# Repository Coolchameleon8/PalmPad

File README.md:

PalmPad
A single handed keyboard based on the hackclub hackpad. Uses a resistor ladder and custom qmk firmware to allow for more inputs than the seeduino xiao has room for.
This is still a work in progress and the case is just temporary. The final version will look similar to a joystick. It is however difficult to design the joystick without the pcb as it has to be broken into parts. This document will be updated later on.

Prototype of the palmpad, just used to test electronics and clearances.
Onshape Link:
https://cad.onshape.com/documents/9e26ee7e9571adbf7a7901c8/w/e33cc611a5f829e6b25b9a69/e/7c23ee493dd5f25881813654?renderMode=0&uiState=69e04b46a869df219ed1fa1f

Wiring schematic for the palmpad

The PCB design

How the case fits together

BOM:
*Seeeduino xiao rp2040
*16x SK6812 MINI-E LEDs
*2x EC11 Rotary encoders
*14x MX-Style switches
*10x through-hole 1N4148 Diodes
*1x 0.91 inch OLED display
*14x white blank DSA keycaps
*4x M3x16mm screws

NOT in hackpad kit
*Assorted wire
*6 10nF smd 1206 capacitors
*6 1k Ohm smd 1206 capacitors
*7 200k Ohm smd 1206 capacitors
*5 100k Ohm smd 1206 capacitors

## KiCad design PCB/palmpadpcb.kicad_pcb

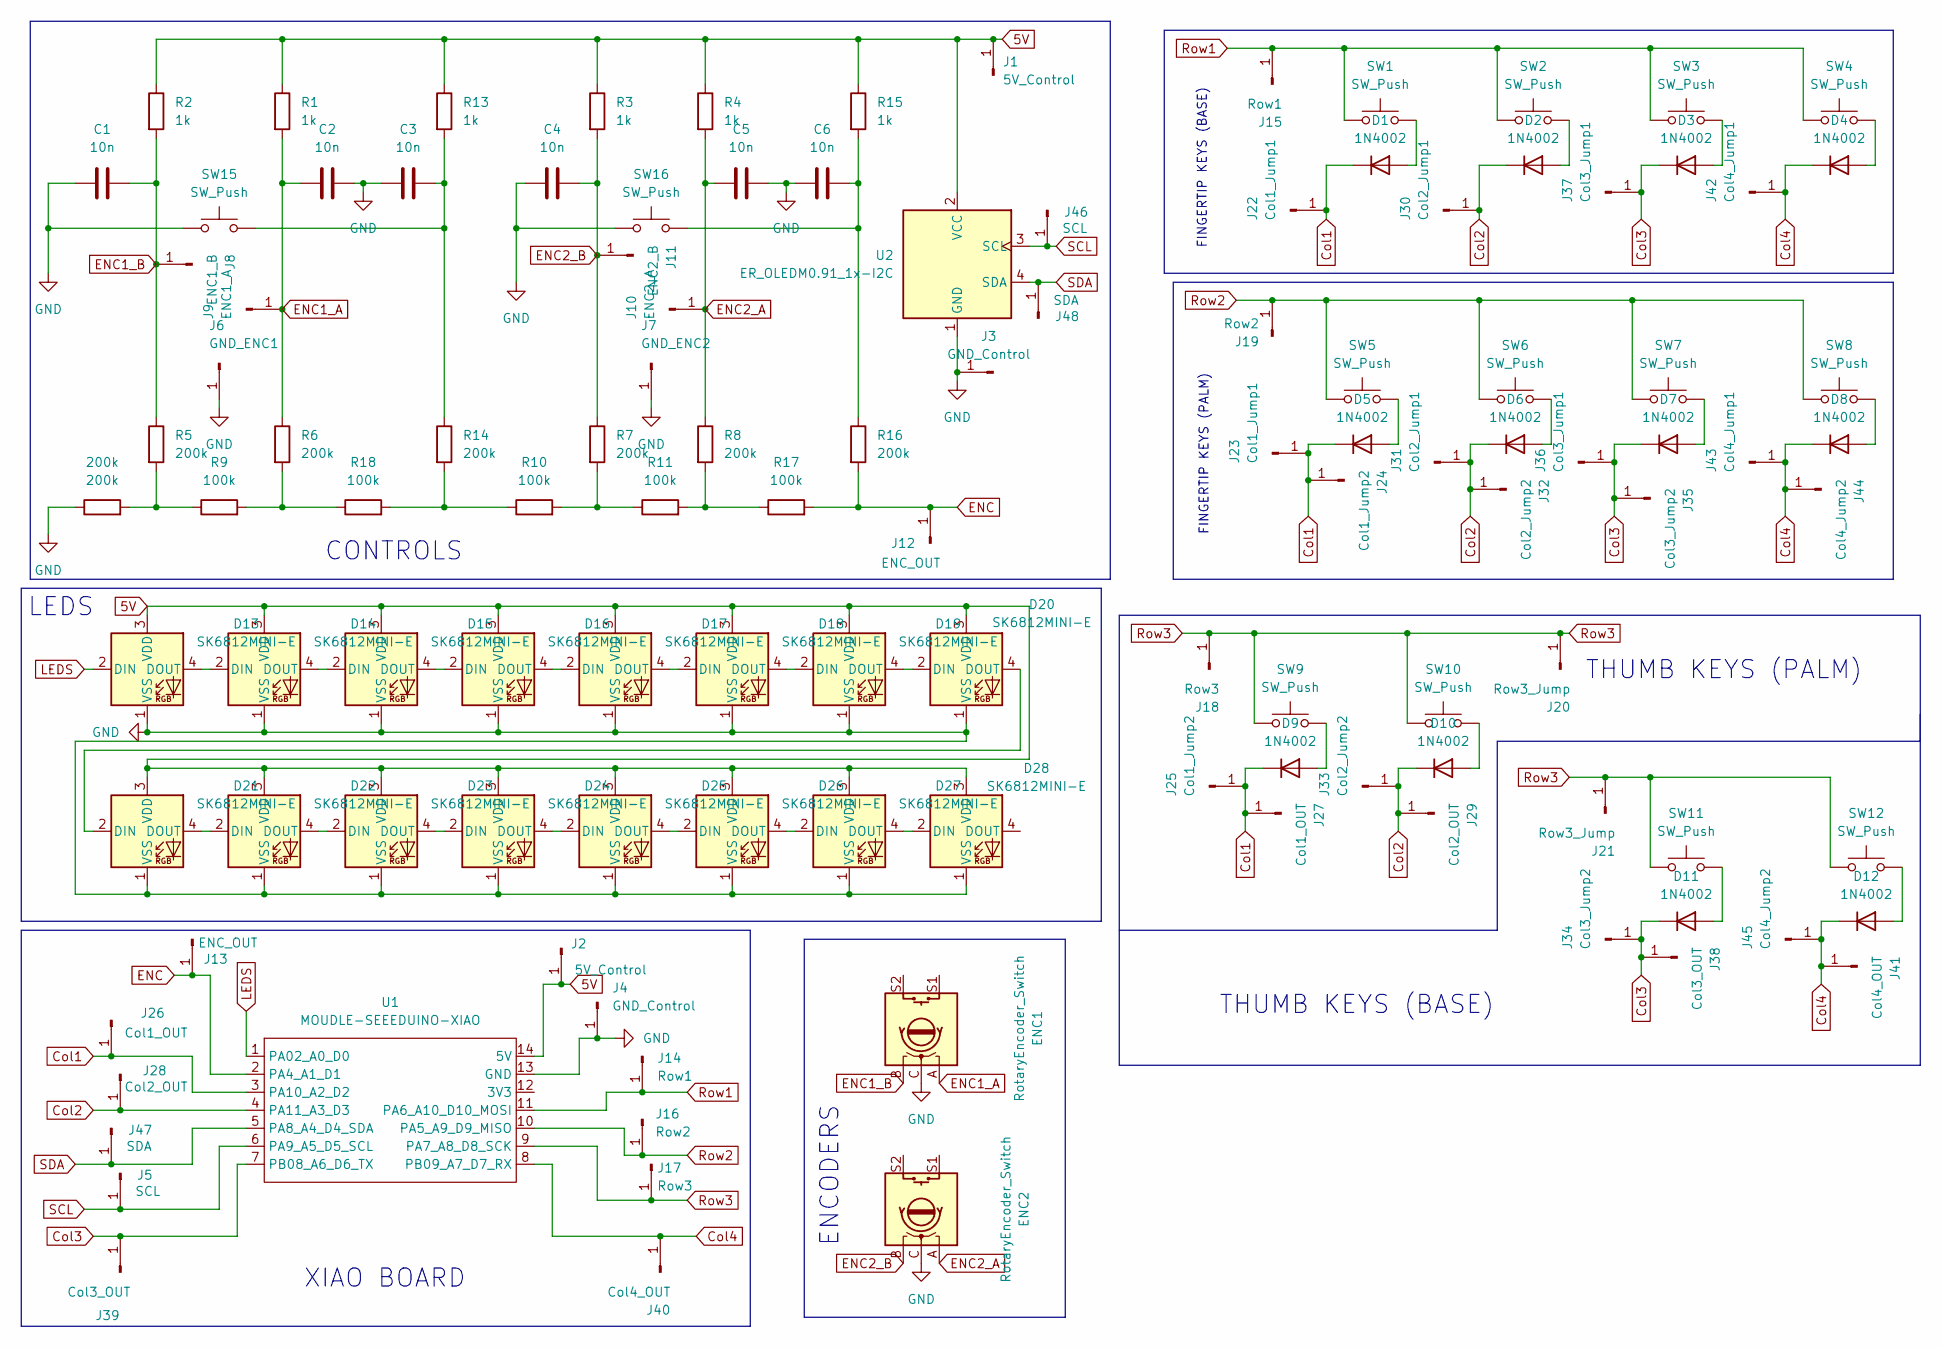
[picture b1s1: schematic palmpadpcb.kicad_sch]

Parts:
200k: 200k; R_Axial_DIN0207_L6.3mm_D2.5mm_P10.16mm_Horizontal
C1, C2, C3, C4, C5, C6: 10n; CP_Axial_L10.0mm_D4.5mm_P15.00mm_Horizontal
D1, D2, D3, D4, D5, D6, D7, D8, D9, D10, D11, D12: 1N4002; D_DO-41_SOD81_P10.16mm_Horizontal
D13, D14, D15, D16, D17, D18, D19, D20, D21, D22, D23, D24, D25, D26, D27, D28: SK6812MINI-E; LED_SK6812MINI-E_3.2x2.8mm_P1.5mm_ReverseMount
ENC1, ENC2: RotaryEncoder_Switch; RotaryEncoder_Alps_EC11E-Switch_Vertical_H20mm
J1, J2: 5V_Control; PinHeader_1x01_P2.00mm_Vertical
J3, J4: GND_Control; PinHeader_1x01_P2.00mm_Vertical
J5, J46: SCL; PinHeader_1x01_P2.00mm_Vertical
J6: GND_ENC1; PinHeader_1x01_P2.00mm_Vertical
J7: GND_ENC2; PinHeader_1x01_P2.00mm_Vertical
J8: ENC1_B; PinHeader_1x01_P2.00mm_Vertical
J9: ENC1_A; PinHeader_1x01_P2.00mm_Vertical
J10: ENC2_A; PinHeader_1x01_P2.00mm_Vertical
J11: ENC2_B; PinHeader_1x01_P2.00mm_Vertical
J12, J13: ENC_OUT; PinHeader_1x01_P2.00mm_Vertical
J14, J15: Row1; PinHeader_1x01_P2.00mm_Vertical
J16, J19: Row2; PinHeader_1x01_P2.00mm_Vertical
J17, J18: Row3; PinHeader_1x01_P2.00mm_Vertical
J20, J21: Row3_Jump; PinHeader_1x01_P2.00mm_Vertical
J22, J23: Col1_Jump1; PinHeader_1x01_P2.00mm_Vertical
J24, J25: Col1_Jump2; PinHeader_1x01_P2.00mm_Vertical
J26, J27: Col1_OUT; PinHeader_1x01_P2.00mm_Vertical
J28, J29: Col2_OUT; PinHeader_1x01_P2.00mm_Vertical
J30, J31: Col2_Jump1; PinHeader_1x01_P2.00mm_Vertical
J32, J33: Col2_Jump2; PinHeader_1x01_P2.00mm_Vertical
J34, J35: Col3_Jump2; PinHeader_1x01_P2.00mm_Vertical
J36, J37: Col3_Jump1; PinHeader_1x01_P2.00mm_Vertical
J38, J39: Col3_OUT; PinHeader_1x01_P2.00mm_Vertical
J40, J41: Col4_OUT; PinHeader_1x01_P2.00mm_Vertical
J42, J43: Col4_Jump1; PinHeader_1x01_P2.00mm_Vertical
J44, J45: Col4_Jump2; PinHeader_1x01_P2.00mm_Vertical
J47, J48: SDA; PinHeader_1x01_P2.00mm_Vertical
R1, R2, R3, R4, R13, R15: 1k; R_Axial_DIN0207_L6.3mm_D2.5mm_P10.16mm_Horizontal
R5, R6, R7, R8, R14, R16: 200k; R_Axial_DIN0207_L6.3mm_D2.5mm_P10.16mm_Horizontal
R9, R10, R11, R17, R18: 100k; R_Axial_DIN0207_L6.3mm_D2.5mm_P10.16mm_Horizontal
SW1, SW2, SW3, SW4, SW5, SW6, SW7, SW8, SW9, SW10, SW11, SW12, SW15, SW16: SW_Push; SW_Cherry_MX_1.00u_PCB
U1: MOUDLE-SEEEDUINO-XIAO; XIAO-Generic-Hybrid-14P-2.54-21X17.8MM
U2: ER_OLEDM0.91_1x-I2C

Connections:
5V: D13.3 (VDD), D14.3 (VDD), D15.3 (VDD), D16.3 (VDD), D17.3 (VDD), D18.3 (VDD), D19.3 (VDD), D20.3 (VDD), D21.3 (VDD), D22.3 (VDD), D23.3 (VDD), D24.3 (VDD), D25.3 (VDD), D26.3 (VDD), D27.3 (VDD), D28.3 (VDD), J1.1 (Pin_1_1), J2.1 (Pin_1_1), R1.1, R2.1, R3.1, R4.1, R13.1, R15.1, U1.14 (5V), U2.2 (VCC)
Col1: D1.1 (K), D5.1 (K), D9.1 (K), J22.1 (Pin_1_1), J23.1 (Pin_1_1), J24.1 (Pin_1_1), J25.1 (Pin_1_1), J26.1 (Pin_1_1), J27.1 (Pin_1_1), U1.3 (PA10_A2_D2)
Col2: D2.1 (K), D6.1 (K), D10.1 (K), J28.1 (Pin_1_1), J29.1 (Pin_1_1), J30.1 (Pin_1_1), J31.1 (Pin_1_1), J32.1 (Pin_1_1), J33.1 (Pin_1_1), U1.4 (PA11_A3_D3)
Col3: D3.1 (K), D7.1 (K), D11.1 (K), J34.1 (Pin_1_1), J35.1 (Pin_1_1), J36.1 (Pin_1_1), J37.1 (Pin_1_1), J38.1 (Pin_1_1), J39.1 (Pin_1_1), U1.7 (PB08_A6_D6_TX)
Col4: D4.1 (K), D8.1 (K), D12.1 (K), J40.1 (Pin_1_1), J41.1 (Pin_1_1), J42.1 (Pin_1_1), J43.1 (Pin_1_1), J44.1 (Pin_1_1), J45.1 (Pin_1_1), U1.8 (PB09_A7_D7_RX)
ENC: J12.1 (Pin_1_1), J13.1 (Pin_1_1), R16.2, R17.2, U1.2 (PA4_A1_D1)
ENC1_A: C2.1, ENC1.A, J9.1 (Pin_1_1), R1.2, R6.1
ENC1_B: C1.2, ENC1.B, J8.1 (Pin_1_1), R2.2, R5.1
ENC2_A: C5.1, ENC2.A, J10.1 (Pin_1_1), R4.2, R8.1
ENC2_B: C4.2, ENC2.B, J11.1 (Pin_1_1), R3.2, R7.1
GND: 200k.1, C1.1, C2.2, C3.1, C4.1, C5.2, C6.1, D13.1 (VSS), D14.1 (VSS), D15.1 (VSS), D16.1 (VSS), D17.1 (VSS), D18.1 (VSS), D19.1 (VSS), D20.1 (VSS), D21.1 (VSS), D22.1 (VSS), D23.1 (VSS), D24.1 (VSS), D25.1 (VSS), D26.1 (VSS), D27.1 (VSS), D28.1 (VSS), ENC1.C, ENC2.C, J3.1 (Pin_1_1), J4.1 (Pin_1_1), J6.1 (Pin_1_1), J7.1 (Pin_1_1), SW15.1, SW16.1, U1.13 (GND), U2.1 (GND); also elsewhere on the board
LEDS: D13.2 (DIN), U1.1 (PA02_A0_D0)
unnamed: C3.2, R13.2, R14.1, SW15.2
unnamed: C6.2, R15.2, R16.1, SW16.2
unnamed: D1.2 (A), SW1.2
unnamed: D2.2 (A), SW2.2
unnamed: D3.2 (A), SW3.2
unnamed: D4.2 (A), SW4.2
unnamed: D5.2 (A), SW5.2
unnamed: D6.2 (A), SW6.2
unnamed: D7.2 (A), SW7.2
unnamed: D8.2 (A), SW8.2
unnamed: D9.2 (A), SW9.2
unnamed: D10.2 (A), SW10.2
unnamed: D11.2 (A), SW11.2
unnamed: D12.2 (A), SW12.2
unnamed: D13.4 (DOUT), D14.2 (DIN)
unnamed: D14.4 (DOUT), D15.2 (DIN)
unnamed: D15.4 (DOUT), D16.2 (DIN)
unnamed: D16.4 (DOUT), D17.2 (DIN)
unnamed: D17.4 (DOUT), D18.2 (DIN)
unnamed: D18.4 (DOUT), D19.2 (DIN)
unnamed: D19.4 (DOUT), D20.2 (DIN)
unnamed: D20.4 (DOUT), D21.2 (DIN)
unnamed: D21.4 (DOUT), D22.2 (DIN)
unnamed: D22.4 (DOUT), D23.2 (DIN)
unnamed: D23.4 (DOUT), D24.2 (DIN)
unnamed: D24.4 (DOUT), D25.2 (DIN)
unnamed: D25.4 (DOUT), D26.2 (DIN)
unnamed: D26.4 (DOUT), D27.2 (DIN)
unnamed: D27.4 (DOUT), D28.2 (DIN)
unnamed: R10.1, R14.2, R18.2
unnamed: R7.2, R10.2, R11.1
unnamed: R8.2, R11.2, R17.1
unnamed 44: 200k.2, R5.2, R9.1; also elsewhere on the board
unnamed: R6.2, R9.2, R18.1
Row1: J14.1 (Pin_1_1), J15.1 (Pin_1_1), SW1.1, SW2.1, SW3.1, SW4.1, U1.11 (PA6_A10_D10_MOSI)
Row2: J16.1 (Pin_1_1), J19.1 (Pin_1_1), SW5.1, SW6.1, SW7.1, SW8.1, U1.10 (PA5_A9_D9_MISO)
Row3: J17.1 (Pin_1_1), J18.1 (Pin_1_1), J20.1 (Pin_1_1), J21.1 (Pin_1_1), SW9.1, SW10.1, SW11.1, SW12.1, U1.9 (PA7_A8_D8_SCK)
SCL: J5.1 (Pin_1_1), J46.1 (Pin_1_1), U1.6 (PA9_A5_D5_SCL), U2.3 (SCL)
SDA: J47.1 (Pin_1_1), J48.1 (Pin_1_1), U1.5 (PA8_A4_D4_SDA), U2.4 (SDA)

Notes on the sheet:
CONTROLS
THUMB KEYS (BASE)
FINGERTIP KEYS (PALM)
FINGERTIP KEYS (BASE)
ENCODERS
LEDS
THUMB KEYS (PALM)
XIAO BOARD

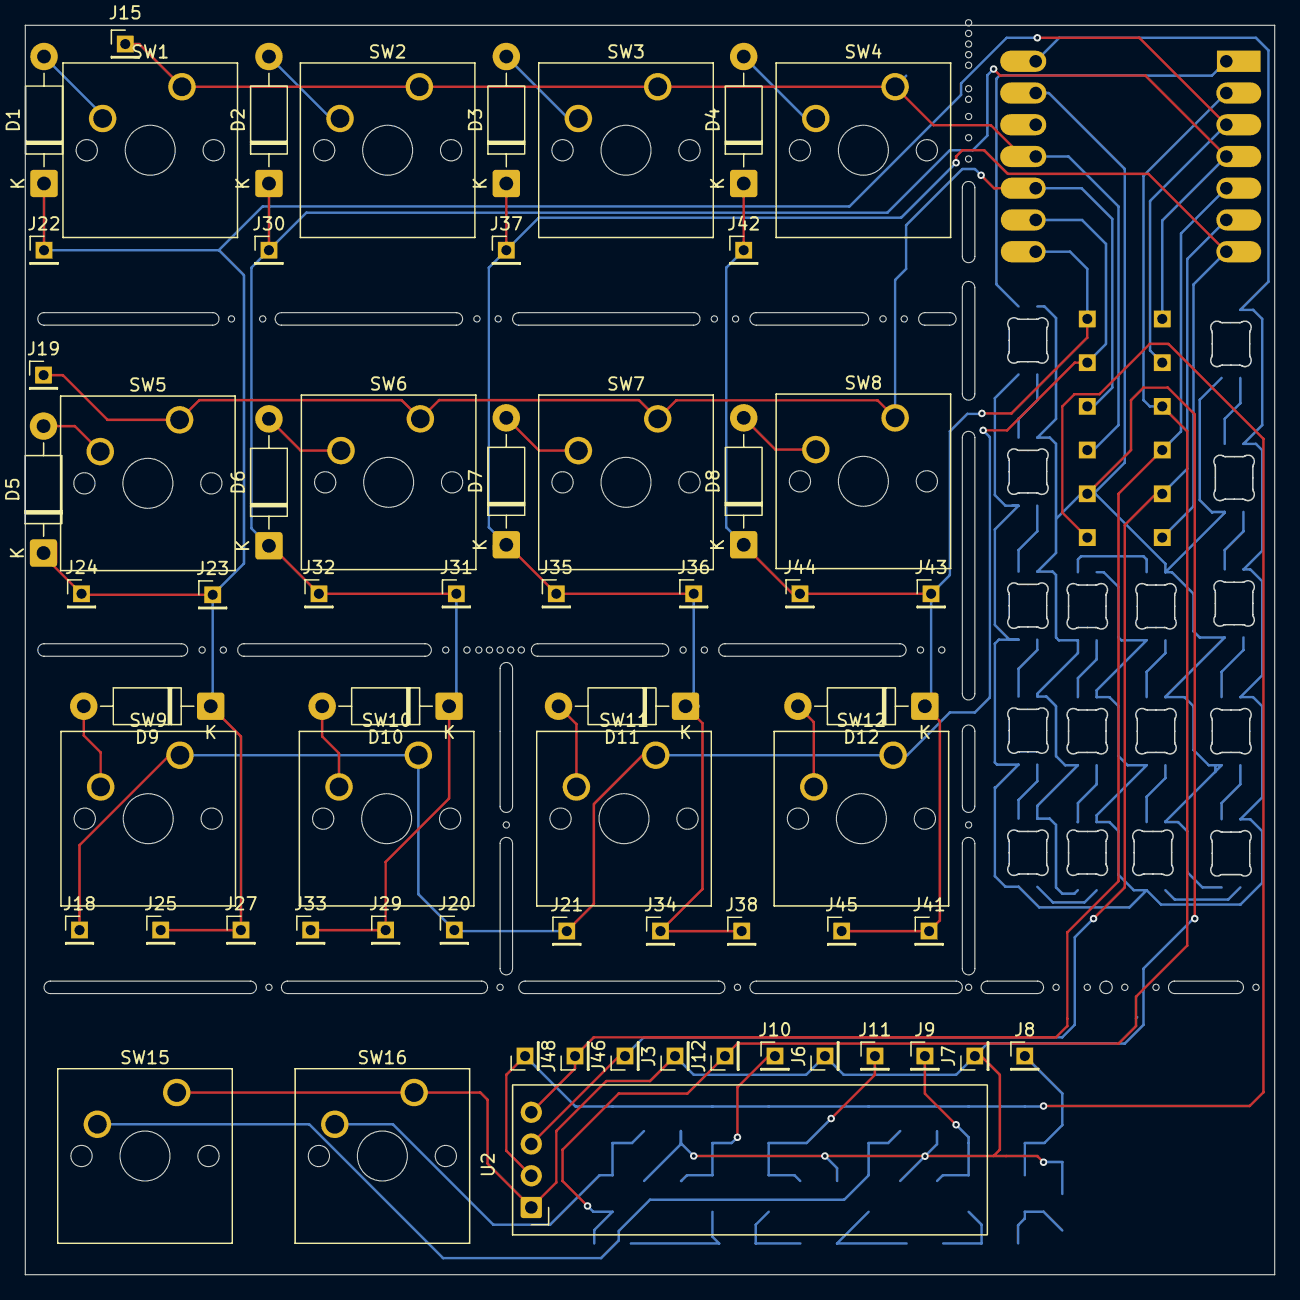
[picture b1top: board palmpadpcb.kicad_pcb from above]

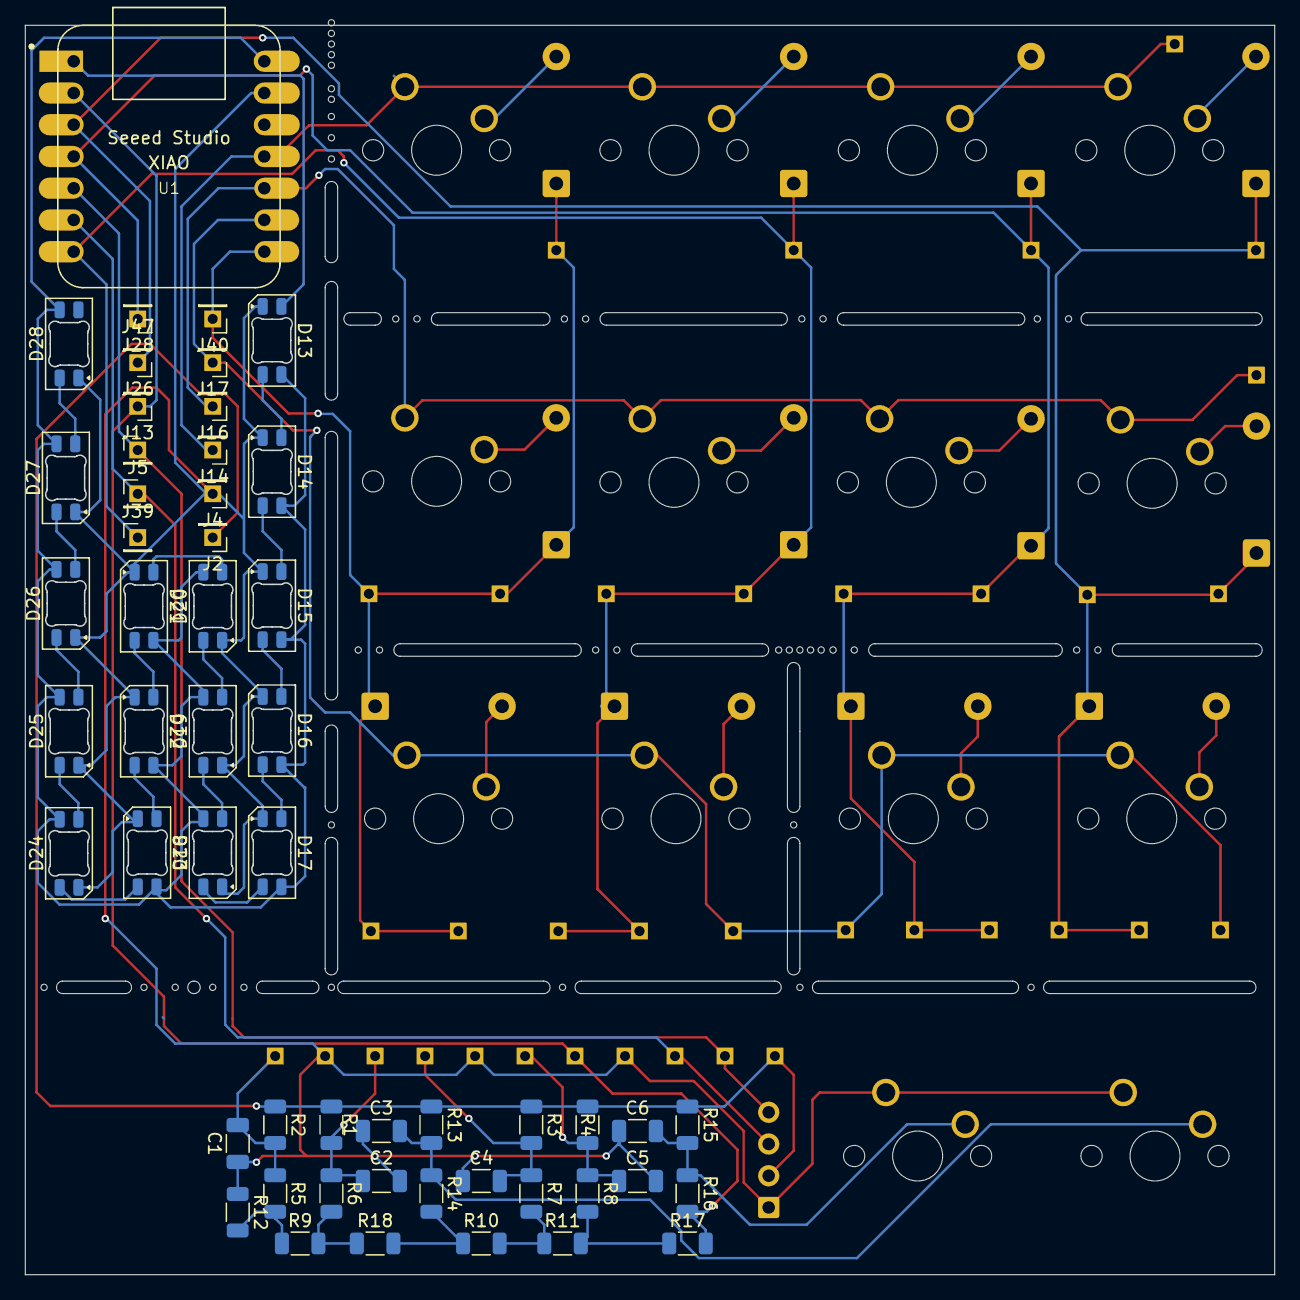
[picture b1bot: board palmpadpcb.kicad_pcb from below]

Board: 2 copper layers, 99.9 x 99.9 mm, 116 parts (53 on the bottom side), 51 nets.

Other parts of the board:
R12: 200k; R_1206_3216Metric

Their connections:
GND: R12.1; also elsewhere on the board
unnamed 44: R12.2; also elsewhere on the board

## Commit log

2026-04-01 Palmpad prototype 1 without firmware
2026-04-01 firmware
2026-04-16 Revision 2
2026-04-16 firmware revision
